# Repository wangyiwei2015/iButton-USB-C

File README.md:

# iButton (USB-C)
 [English](README_EN.md)

为配备 USB Type-C 接口的 iOS 设备提供外置的物理按键，可自定义功能。

由 STM32 上的 USB HID middleware 实现，模拟了外置鼠标上的自定义按键。

按键功能在`辅助功能` - `触控` - `辅助触控` 中设置。

## 构建环境

- 主控固件管理和代码生成: **STM32CubeMX**
- 代码编辑器/开发工具: **CLion**
- 编译器: **gcc-arm-none-eabi**
- 烧录工具: **ST-Link Utility** or **STM32CubeProgrammer** or **OpenOCD**

注意：使用 STM32CubeMX 时，可能会要求登录 ST account 。

## 项目文件

- [iButton-FW](iButton-FW1/): 主要固件代码 (CLion/CubeIDE)
- [STM32-iButton](STM32-iButton-v3/): 主板 (立创EDA Pro)
- [EdgeLink](EdgeLink2/): ST-Link V2 to EdgeLink 转接器 (KiCAD)
- [EdgDbg](EdgDbg3/): ST-Link 带有 EdgeLink 连接器 (立创EDA Pro)
- [Case3D](Case3D/): 3D 外壳模型 (Shapr3D)
- [Datasheet](Datasheet/): 参考资料 (PDF)

其中 EdgDbg（Edge-Debugger）的基底是 [开源 ST-Link-V2](https://oshwhub.com/CYIIOT/ST_LINK-V2_1)，将 SWD 相关接口改成 EdgeLink 而成。

## Notes

BOOT0默认下拉到GND；要使STM32启动到下载模式，需要将BOOT0置高。在EdgeLink金手指连接器处，BOOT0直接连接VCC，这样当板卡插入EdgeLink调试器时就会进入下载模式。VCC可选5V或3V3，STM32微控制器的BOOT0是否接受5V输入需要视型号而定。对于STM32L052系列，BOOT0最大输入为VDD+4V，因此可以安全连接。

要烧录和调试STM32-iButton-v3主板，需要使用EdgDbg硬件或EdgeLink+ST-Link（它们是等价的）。

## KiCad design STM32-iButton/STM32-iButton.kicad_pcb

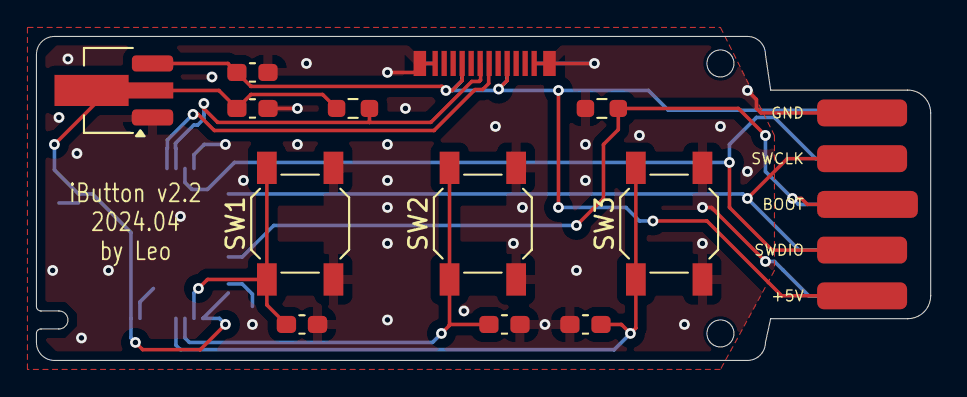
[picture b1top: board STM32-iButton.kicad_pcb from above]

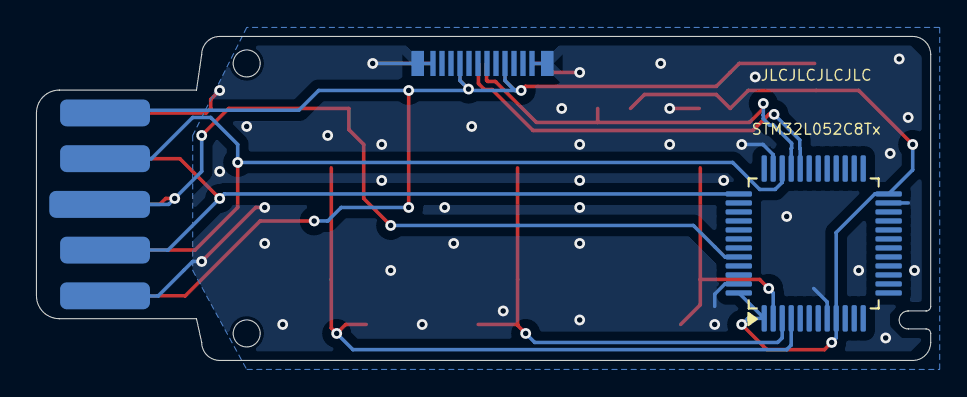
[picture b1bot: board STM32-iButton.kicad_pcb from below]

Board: 2 copper layers, 49.7 x 18.0 mm, 15 parts (2 on the bottom side), 11 nets.

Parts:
C1, C2: 10uF; C_0603_1608Metric_Pad1.08x0.95mm_HandSolder
C3, C4, C5: 4.7uF; C_0603_1608Metric_Pad1.08x0.95mm_HandSolder
J1, J2: Conn_SWD; SWD5-Gold
P1: USB_C_2.0; USB_C_Male
R1: 1.5k; R_0603_1608Metric_Pad0.98x0.95mm_HandSolder
R2: 10k; R_0603_1608Metric_Pad0.98x0.95mm_HandSolder
SW1, SW2, SW3: Button_user; SW_SPST_SKQG_WithoutStem
U1: STM32L052C8Tx; LQFP-48_7x7mm_P0.5mm
U2: AMS1117-3.3; SOT-89-3_Handsoldering

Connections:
+3.3V: C1.1, R1.1, U1.1 (VDD), U1.9 (VDDA), U1.24 (VDD), U1.48 (VDD), U2.2 (VO)
+5V: C2.1, J1.1, J2.1, P1.A4 (VBUS), P1.A9 (VBUS), P1.B4 (VBUS), P1.B9 (VBUS), U2.3 (VI)
/Boot: J1.3, J2.3, R2.1, U1.44 (BOOT0)
/Btn1: C3.1, SW1.1, U1.2 (PC13)
/Btn2: C4.1, SW2.1, U1.3 (PC14)
/Btn3: C5.1, SW3.1, U1.4 (PC15)
/D+: P1.A6 (D+), R1.2, U1.33 (PA12)
/D-: P1.A7 (D-), U1.32 (PA11)
/SWCLK: J1.4, J2.4, U1.37 (PA14)
/SWDIO: J1.2, J2.2, U1.34 (PA13)
GND: C1.2, C2.2, C3.2, C4.2, C5.2, J1.5, J2.5, P1.A1 (GND), P1.A12 (GND), P1.B1 (GND), P1.B12 (GND), P1.S1 (SHIELD), R2.2, SW1.2, SW2.2, SW3.2, U1.8 (VSSA), U1.23 (VSS), U1.35 (VSS), U1.47 (VSS), U2.1 (GND)

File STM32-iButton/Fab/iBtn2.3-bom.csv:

"Id";"指示符";"封装";"数量";"名称";"供应商和参考";
1;"U1";"LQFP-48_7x7mm_P0.5mm";1;"STM32L052C8Tx";;;
2;"C3,C5,C4";"C_0603_1608Metric_Pad1.08x0.95mm_HandSolder";3;"4.7uF";;;
3;"R1";"R_0603_1608Metric_Pad0.98x0.95mm_HandSolder";1;"1.5k";;;
4;"J2,J1";"SWD5-Gold";2;"Conn_SWD";;;
5;"U2";"SOT-89-3_Handsoldering";1;"AMS1117-3.3";;;
6;"C2,C1";"C_0603_1608Metric_Pad1.08x0.95mm_HandSolder";2;"10uF";;;
7;"SW2,SW1,SW3";"SW_SPST_SKQG_WithoutStem";3;"Button_user";;;
8;"P1";"USB_C_Male";1;"USB_C_2.0";;;
9;"R2";"R_0603_1608Metric_Pad0.98x0.95mm_HandSolder";1;"10k";;;

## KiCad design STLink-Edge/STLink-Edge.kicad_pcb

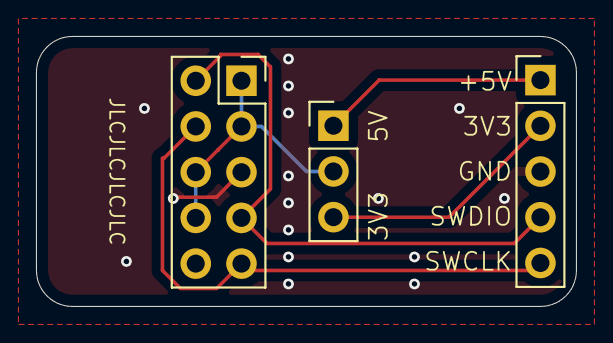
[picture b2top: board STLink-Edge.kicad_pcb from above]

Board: 2 copper layers, 30.0 x 15.0 mm, 3 parts (0 on the bottom side), 6 nets.

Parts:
J1: Conn_edge_socket; PinSocket_2x05_P2.54mm_Vertical
J3: Conn_STLink2; PinHeader_1x05_P2.54mm_Vertical
SW1: SW_Push_SPDT; PinHeader_1x03_P2.54mm_Vertical

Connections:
+3.3V: J3.2, SW1.3 (C)
+5V: J3.1, SW1.1 (A)
/Boot: J1.1, J1.3, J1.6, J1.8, SW1.2 (B)
/SWCLK: J1.4, J1.9, J3.5
/SWDIO: J1.2, J1.7, J3.4
GND: J1.5, J1.10, J3.3

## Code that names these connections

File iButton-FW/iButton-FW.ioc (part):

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Mcu.Name=STM32L052C(6-8)Tx
Mcu.Package=LQFP48
Mcu.UserName=STM32L052C8Tx
PA11.Mode=Device
PA11.Signal=USB_DM
PA12.Mode=Device
PA12.Signal=USB_DP
PC13.GPIOParameters=GPIO_PuPd,GPIO_Label
PC13.GPIO_Label=Btn1
PC13.GPIO_PuPd=GPIO_PULLUP
PC13.Signal=GPIO_Input
PC14-OSC32_IN.GPIOParameters=GPIO_PuPd,GPIO_Label
PC14-OSC32_IN.GPIO_Label=Btn2
PC14-OSC32_IN.GPIO_PuPd=GPIO_PULLUP
PC14-OSC32_IN.Signal=GPIO_Input
PC15-OSC32_OUT.GPIOParameters=GPIO_PuPd,GPIO_Label
PC15-OSC32_OUT.GPIO_Label=Btn3
PC15-OSC32_OUT.GPIO_PuPd=GPIO_PULLUP
PC15-OSC32_OUT.Signal=GPIO_Input
RCC.HSE_VALUE=8000000
RCC.SYSCLKFreq_VALUE=16000000
RCC.SYSCLKSource=RCC_SYSCLKSOURCE_HSI
board=custom

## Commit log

2024-03-30 init
2024-03-30 add fab release
2024-03-31 critical fix: 5V power
2024-03-31 edgelink 2.1
2024-03-31 critical fix
2024-03-31 added stlink edge 3
2024-03-31 init FW1 project
2024-03-31 nonsense
2024-03-31 added 3D case
2024-04-01 added datasheets
2024-04-01 arranged
2024-04-01 updated silks
2024-04-07 add front ver
2024-04-07 gen fab bom pos
2024-04-14 changed codes
2024-04-15 updated model
2024-04-17 FW for EdgDbg
2024-04-23 removed old project files
2024-04-23 added readme for edgelink
